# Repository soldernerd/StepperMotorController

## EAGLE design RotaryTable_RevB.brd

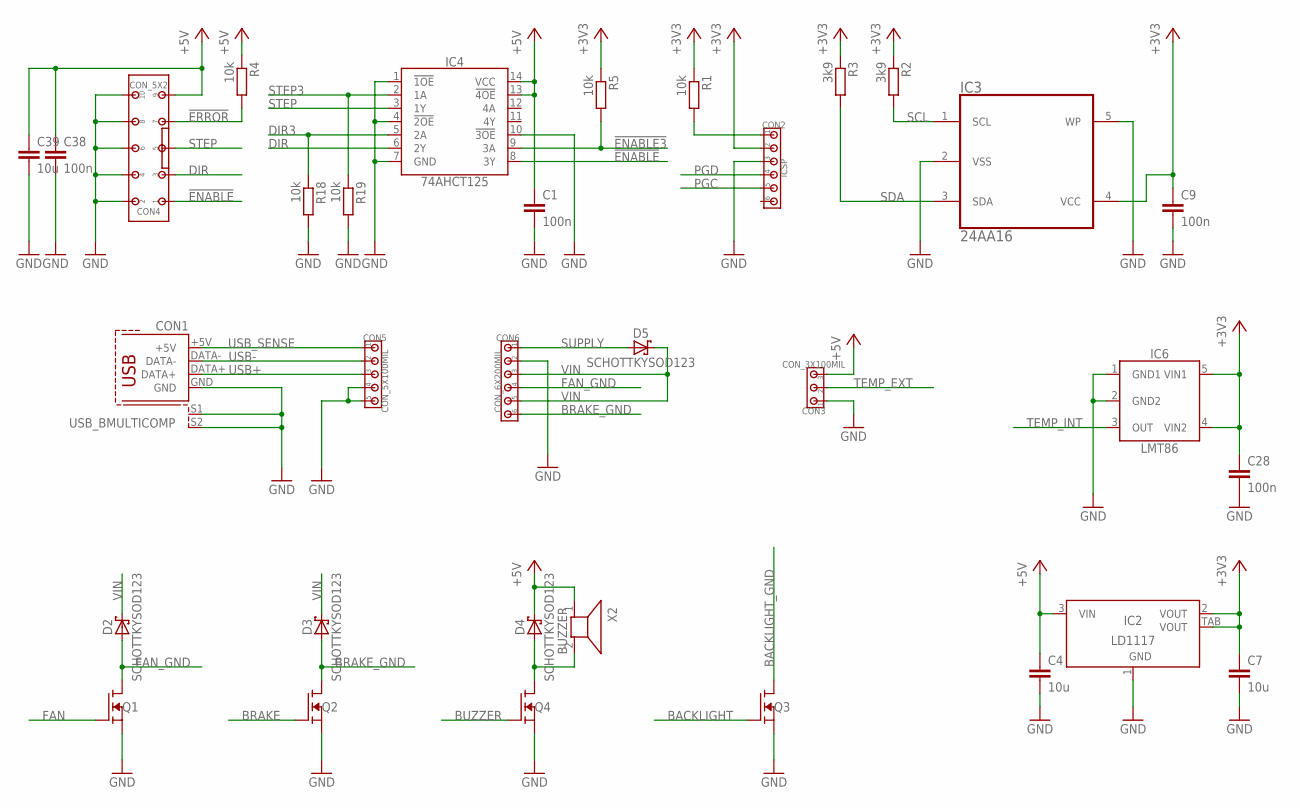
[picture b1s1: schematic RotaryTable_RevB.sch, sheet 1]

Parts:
C1, C9, C28, C38: 100n; C0805
C4, C7, C39: 10u; C0805
CON1: USB_BMULTICOMP; USB_B
CON2: ICSP; 100MIL_6X
CON3: CON_3X100MIL; 100MIL_3X
CON4: CON_5X2; 100MIL_5X2
CON5: CON_5X100MIL; 100MIL_5X
CON6: CON_6X200MIL; 200MIL_6X
D2, D3, D4, D5: SCHOTTKYSOD123; SOD123
IC2: LD1117; SOT223
IC3: 24AA16; SOT-23-5
IC4: 74AHCT125; SO14
IC6: LMT86; SC70-5
Q1, Q2, Q3, Q4: N-FETSOT23; SOT23
R1, R4, R5, R18, R19: 10k; R0805
R2, R3: 3k9; R0805
X2: BUZZER; BUZZER_14MM

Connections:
!ENABLE3!: IC4.9 (3A), R5.2; also elsewhere on the board
!ENABLE!: CON4.1, IC4.8 (3Y)
!ERROR!: CON4.7, R4.2; also elsewhere on the board
!MCLR!: CON2.1, R1.2; also elsewhere on the board
+3V3: C7.1, C9.1, C28.1, CON2.2, IC2.2 (VOUT), IC2.TAB (VOUT), IC3.4 (VCC), IC6.4 (VIN2), IC6.5 (VIN1), R1.1, R2.1, R3.1, R5.1; also elsewhere on the board
+5V: C1.1, C4.1, C38.1, C39.1, CON3.3, CON4.9, D4.C, IC2.3 (VIN), IC4.13 (!4OE!), IC4.14 (VCC), R4.1, X2.1; also elsewhere on the board
BACKLIGHT: Q3.1 (G); also elsewhere on the board
BACKLIGHT_GND: Q3.3 (D); also elsewhere on the board
BRAKE: Q2.1 (G); also elsewhere on the board
BRAKE_GND: CON6.6, D3.A, Q2.3 (D)
BUZZER: Q4.1 (G); also elsewhere on the board
BUZZER_GND: D4.A, Q4.3 (D), X2.2
DIR: CON4.3, IC4.6 (2Y)
DIR3: IC4.5 (2A), R18.1; also elsewhere on the board
FAN: Q1.1 (G); also elsewhere on the board
FAN_GND: CON6.4, D2.A, Q1.3 (D)
GND: C1.2, C4.2, C7.2, C9.2, C28.2, C38.2, C39.2, CON1.GND, CON1.S1, CON1.S2, CON2.3, CON3.1, CON4.2, CON4.4, CON4.6, CON4.8, CON4.10, CON5.4, CON5.5, CON6.2, IC2.1 (GND), IC3.2 (VSS), IC3.5 (WP), IC4.1 (!1OE!), IC4.4 (!2OE!), IC4.7 (GND), IC4.10 (!3OE!), IC6.1 (GND1), IC6.2 (GND2), Q1.2 (S), Q2.2 (S), Q3.2 (S), Q4.2 (S), R18.2, R19.2; also elsewhere on the board
PGC: CON2.5; also elsewhere on the board
PGD: CON2.4; also elsewhere on the board
SCL: IC3.1 (SCL), R2.2; also elsewhere on the board
SDA: IC3.3 (SDA), R3.2; also elsewhere on the board
STEP: CON4.5, IC4.3 (1Y)
STEP3: IC4.2 (1A), R19.1; also elsewhere on the board
SUPPLY: CON6.1, D5.A
TEMP_EXT: CON3.2; also elsewhere on the board
TEMP_INT: IC6.3 (OUT); also elsewhere on the board
USB+: CON1.DATA+, CON5.3; also elsewhere on the board
USB-: CON1.DATA-, CON5.2; also elsewhere on the board
USB_SENSE: CON1.+5V, CON5.1; also elsewhere on the board
VIN: CON6.3, CON6.5, D2.C, D3.C, D5.C; also elsewhere on the board

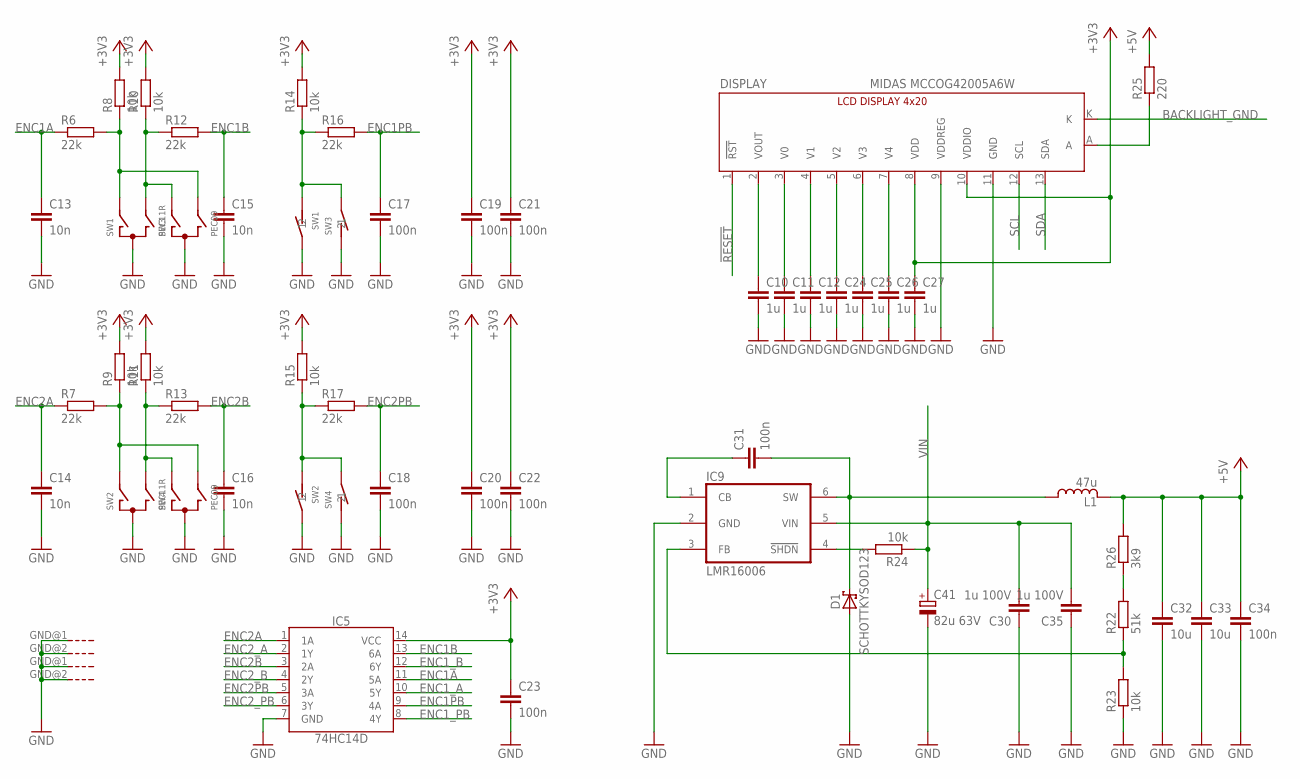
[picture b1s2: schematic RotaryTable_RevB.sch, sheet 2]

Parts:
C10, C11, C12, C24, C25, C26, C27: 1u; C0805
C13, C14, C15, C16: 10n; C0805
C17, C18, C19, C20, C21, C22, C23, C31, C34: 100n; C0805
C30, C35: 1u 100V; C0805
C32, C33: 10u; C0805
C41: 82u 63V; 8MM
D1: SCHOTTKYSOD123; SOD123
DISPLAY: MIDAS MCCOG42005A6W; LCD_4X20_I2C
IC5: 74HC14D; SO14
IC9: LMR16006; SOT-32-6
L1: 47u; SRN5040
R6, R7, R12, R13, R16, R17: 22k; R0805
R8, R9, R10, R11, R14, R15, R23, R24: 10k; R0805
R22: 51k; R0805
R25: 220; R0805
R26: 3k9; R0805
SW1, SW2: PEC11R; ENCODER_BOURNS
SW3, SW4: PEC09

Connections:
!RESET!: DISPLAY.1 (!RST!); also elsewhere on the board
+3V3: C19.1, C20.1, C21.1, C22.1, C23.1, C27.1, DISPLAY.8 (VDD), DISPLAY.10 (VDDIO), IC5.14 (VCC), R8.2, R9.2, R10.2, R11.2, R14.2, R15.2; also elsewhere on the board
+5V: C32.1, C33.1, C34.1, L1.2, R25.2, R26.2; also elsewhere on the board
BACKLIGHT_GND: DISPLAY.K; also elsewhere on the board
ENC1A: C13.1, IC5.11 (5A), R6.1
ENC1B: C15.1, IC5.13 (6A), R12.2
ENC1PB: C17.1, IC5.9 (4A), R16.2
ENC1_A: IC5.10 (5Y); also elsewhere on the board
ENC1_B: IC5.12 (6Y); also elsewhere on the board
ENC1_PB: IC5.8 (4Y); also elsewhere on the board
ENC2A: C14.1, IC5.1 (1A), R7.1
ENC2B: C16.1, IC5.3 (2A), R13.2
ENC2PB: C18.1, IC5.5 (3A), R17.2
ENC2_A: IC5.2 (1Y); also elsewhere on the board
ENC2_B: IC5.4 (2Y); also elsewhere on the board
ENC2_PB: IC5.6 (3Y); also elsewhere on the board
GND: C10.2, C11.2, C12.2, C13.2, C14.2, C15.2, C16.2, C17.2, C18.2, C19.2, C20.2, C21.2, C22.2, C23.2, C24.2, C25.2, C26.2, C27.2, C30.1, C32.2, C33.2, C34.2, C35.1, C41.-, D1.A, DISPLAY.9 (VDDREG), DISPLAY.11 (GND), IC5.7 (GND), IC9.2 (GND), R23.1, SW1.2, SW1.C, SW1.GND@1 (G), SW1.GND@2 (G), SW2.2, SW2.C, SW2.GND@1 (G), SW2.GND@2 (G), SW3.C, SW3.D (1), SW4.C, SW4.D (1); also elsewhere on the board
unnamed: IC9.4 (!SHDN!), R24.2
unnamed: C31.1, IC9.1 (CB)
unnamed: IC9.3 (FB), R22.1, R23.2
unnamed: R22.2, R26.1
unnamed: R15.1, R17.1, SW2.1, SW4.E (2)
unnamed: R10.1, R12.1, SW1.B, SW3.A
unnamed: R6.2, R8.1, SW1.A, SW3.B
unnamed: DISPLAY.A, R25.1
unnamed: R7.2, R9.1, SW2.A, SW4.B
unnamed: R14.1, R16.1, SW1.1, SW3.E (2)
unnamed: R11.1, R13.1, SW2.B, SW4.A
unnamed: C10.1, DISPLAY.2 (VOUT)
unnamed: C11.1, DISPLAY.3 (V0)
unnamed: C26.1, DISPLAY.7 (V4)
unnamed: C25.1, DISPLAY.6 (V3)
unnamed: C24.1, DISPLAY.5 (V2)
unnamed: C12.1, DISPLAY.4 (V1)
SCL: DISPLAY.12 (SCL); also elsewhere on the board
SDA: DISPLAY.13 (SDA); also elsewhere on the board
SWITCH: C31.2, D1.C, IC9.6 (SW), L1.1
VIN: C30.2, C35.2, C41.+, IC9.5 (VIN), R24.1; also elsewhere on the board

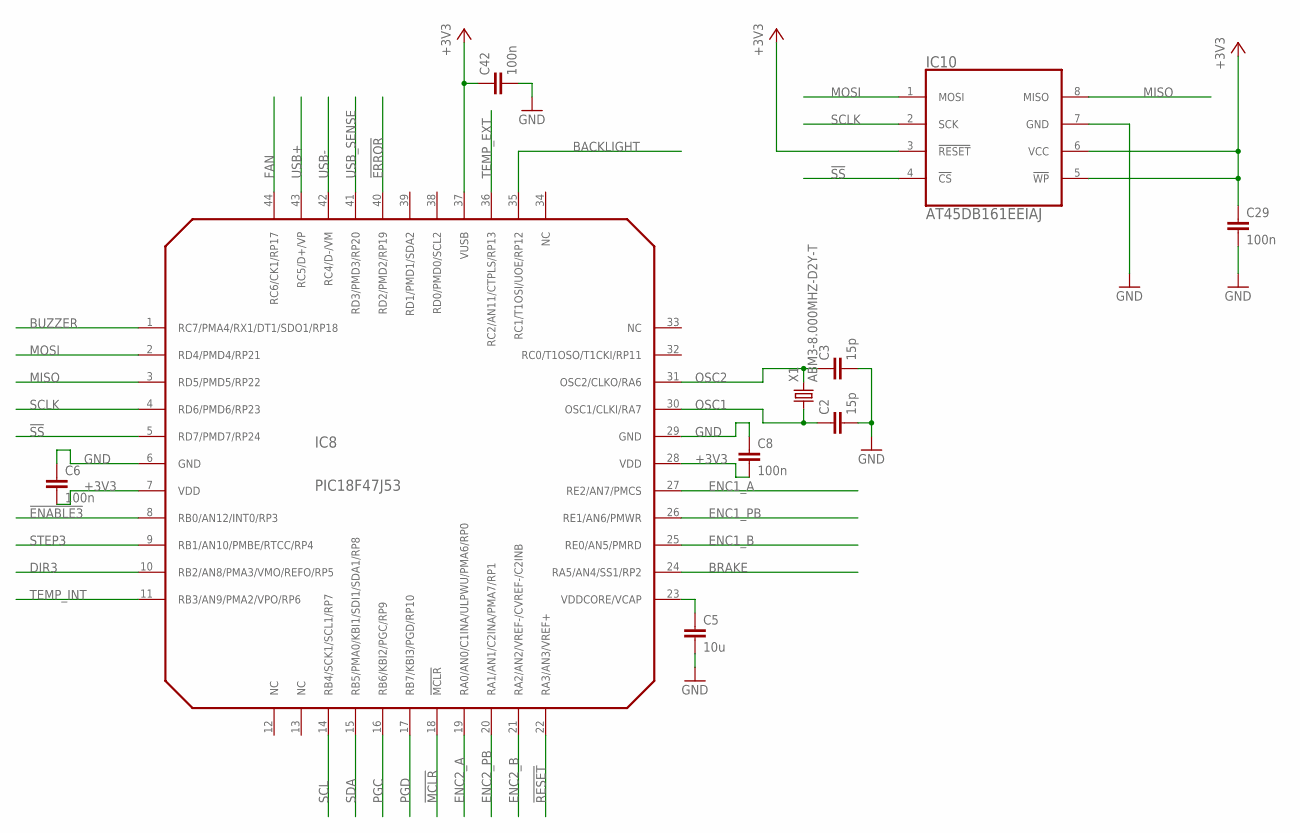
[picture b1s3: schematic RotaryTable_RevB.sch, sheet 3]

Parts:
C2, C3: 15p; C0805
C5: 10u; C0805
C6, C8, C29, C42: 100n; C0805
IC8: PIC18F47J53; TQFP44
IC10: AT45DB161EEIAJ; EIAJ_SOIC8
X1: ABM3-8.000MHZ-D2Y-T; 5X3.2MM

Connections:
!ENABLE3!: IC8.8 (RB0/AN12/INT0/RP3); also elsewhere on the board
!ERROR!: IC8.40 (RD2/PMD2/RP19); also elsewhere on the board
!MCLR!: IC8.18 (!MCLR!); also elsewhere on the board
!RESET!: IC8.22 (RA3/AN3/VREF+); also elsewhere on the board
!SS!: IC8.5 (RD7/PMD7/RP24), IC10.4 (!CS!)
+3V3: C6.2, C8.2, C29.1, C42.1, IC8.7 (VDD), IC8.28 (VDD), IC8.37 (VUSB), IC10.3 (!RESET!), IC10.5 (!WP!), IC10.6 (VCC); also elsewhere on the board
BACKLIGHT: IC8.35 (RC1/T1OSI/UOE/RP12); also elsewhere on the board
BRAKE: IC8.24 (RA5/AN4/SS1/RP2); also elsewhere on the board
BUZZER: IC8.1 (RC7/PMA4/RX1/DT1/SDO1/RP18); also elsewhere on the board
DIR3: IC8.10 (RB2/AN8/PMA3/VMO/REFO/RP5); also elsewhere on the board
ENC1_A: IC8.27 (RE2/AN7/PMCS); also elsewhere on the board
ENC1_B: IC8.25 (RE0/AN5/PMRD); also elsewhere on the board
ENC1_PB: IC8.26 (RE1/AN6/PMWR); also elsewhere on the board
ENC2_A: IC8.19 (RA0/AN0/C1INA/ULPWU/PMA6/RP0); also elsewhere on the board
ENC2_B: IC8.21 (RA2/AN2/VREF-/CVREF-/C2INB); also elsewhere on the board
ENC2_PB: IC8.20 (RA1/AN1/C2INA/PMA7/RP1); also elsewhere on the board
FAN: IC8.44 (RC6/CK1/RP17); also elsewhere on the board
GND: C2.2, C3.2, C5.2, C6.1, C8.1, C29.2, C42.2, IC8.6 (GND), IC8.29 (GND), IC10.7 (GND); also elsewhere on the board
MISO: IC8.3 (RD5/PMD5/RP22), IC10.8 (MISO)
MOSI: IC8.2 (RD4/PMD4/RP21), IC10.1 (MOSI)
unnamed: C5.1, IC8.23 (VDDCORE/VCAP)
OSC1: C2.1, IC8.30 (OSC1/CLKI/RA7), X1.1
OSC2: C3.1, IC8.31 (OSC2/CLKO/RA6), X1.2
PGC: IC8.16 (RB6/KBI2/PGC/RP9); also elsewhere on the board
PGD: IC8.17 (RB7/KBI3/PGD/RP10); also elsewhere on the board
SCL: IC8.14 (RB4/SCK1/SCL1/RP7); also elsewhere on the board
SCLK: IC8.4 (RD6/PMD6/RP23), IC10.2 (SCK)
SDA: IC8.15 (RB5/PMA0/KBI1/SDI1/SDA1/RP8); also elsewhere on the board
STEP3: IC8.9 (RB1/AN10/PMBE/RTCC/RP4); also elsewhere on the board
TEMP_EXT: IC8.36 (RC2/AN11/CTPLS/RP13); also elsewhere on the board
TEMP_INT: IC8.11 (RB3/AN9/PMA2/VPO/RP6); also elsewhere on the board
USB+: IC8.43 (RC5/D+/VP); also elsewhere on the board
USB-: IC8.42 (RC4/D-/VM); also elsewhere on the board
USB_SENSE: IC8.41 (RD3/PMD3/RP20); also elsewhere on the board

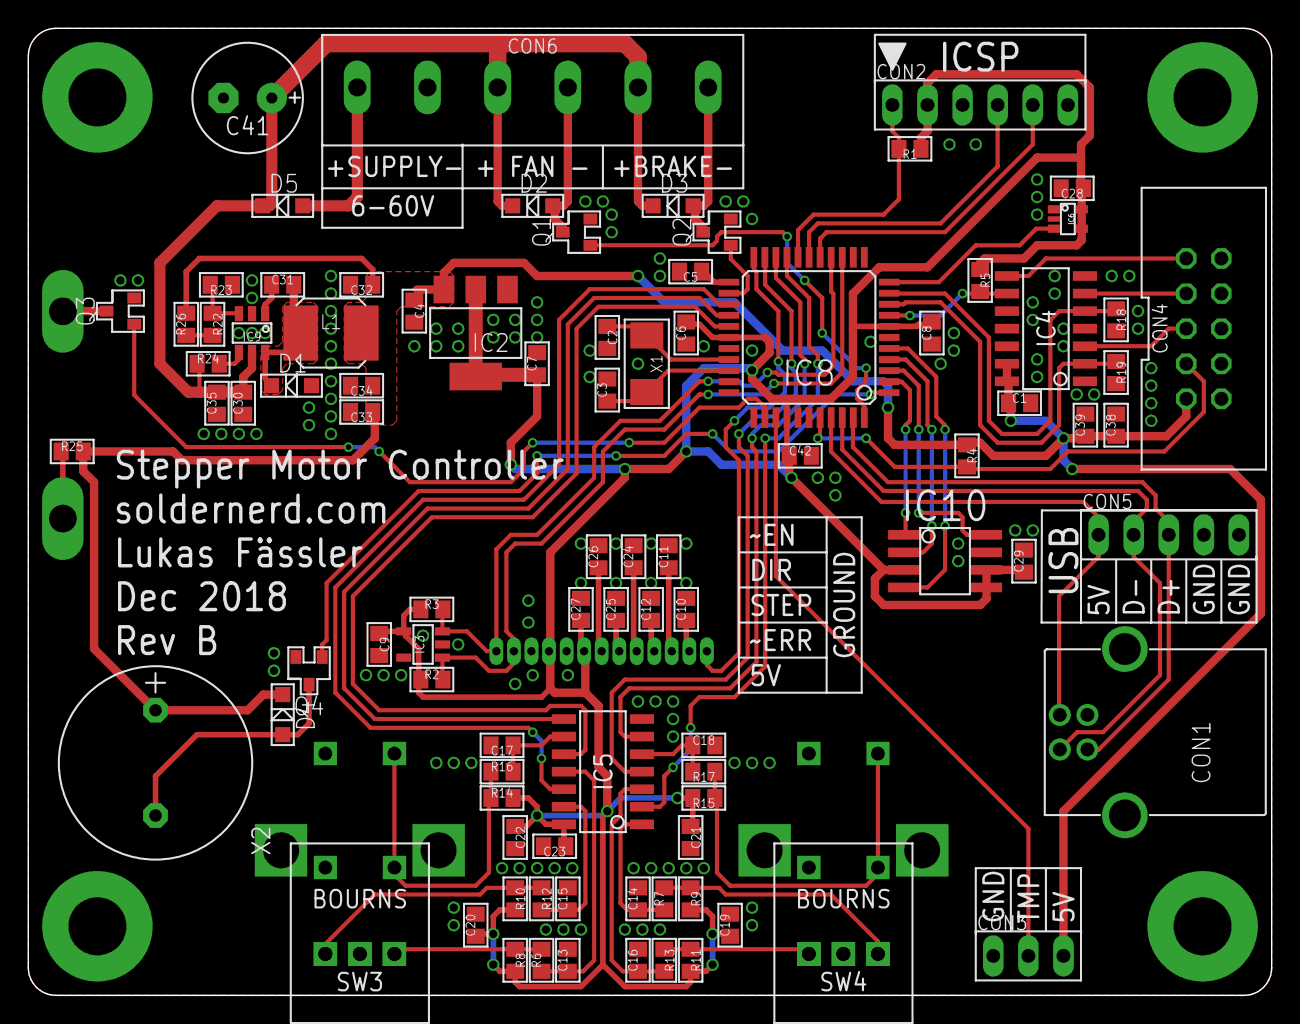
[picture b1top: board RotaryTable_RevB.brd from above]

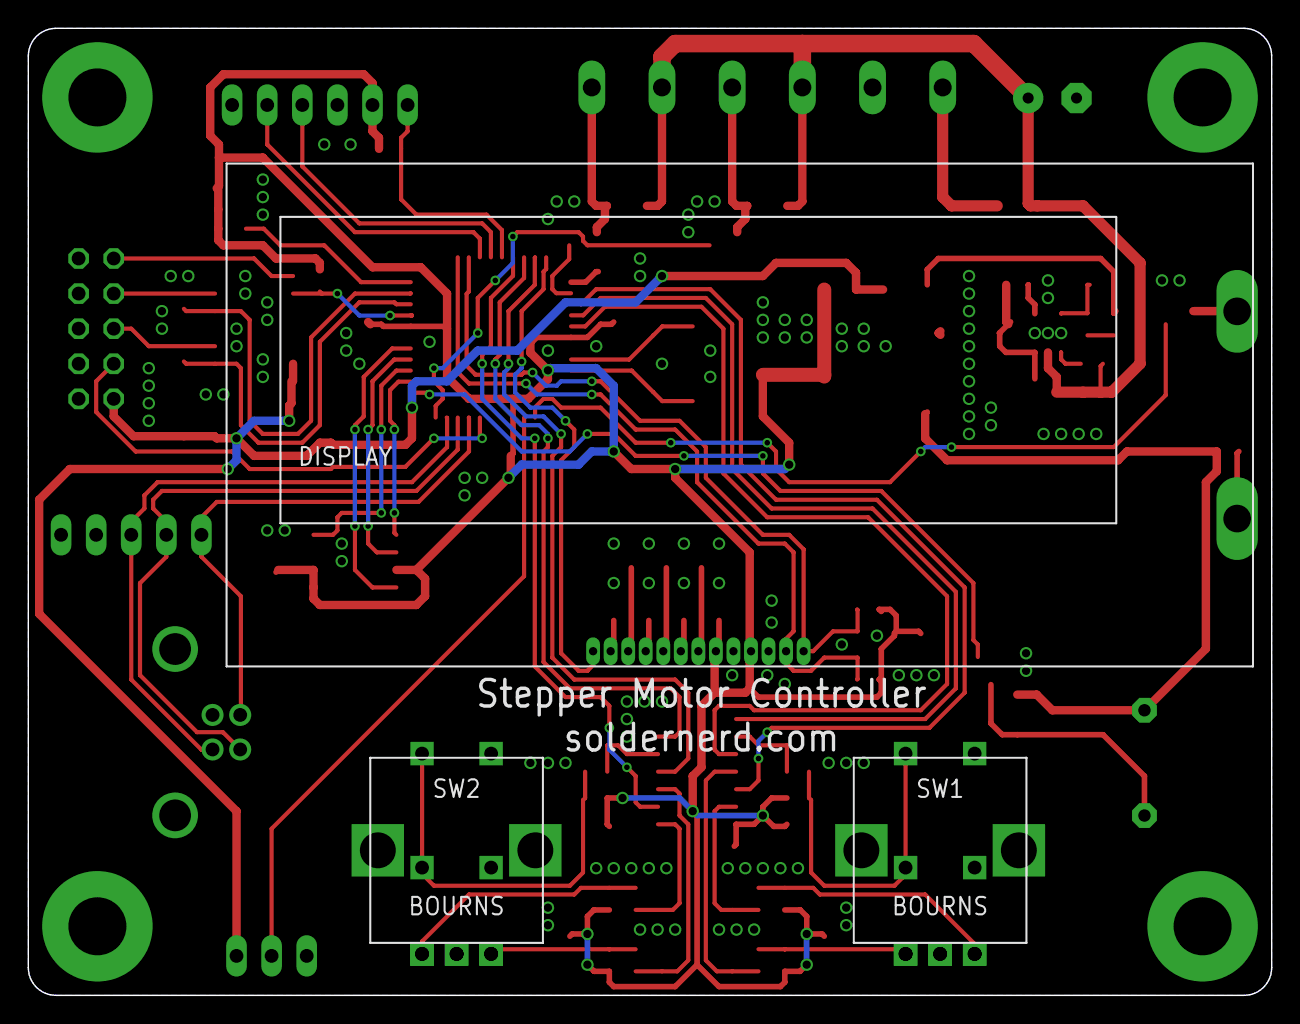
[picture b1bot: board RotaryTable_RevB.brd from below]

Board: 2 copper layers, 90.0 x 70.0 mm, 94 parts (3 on the bottom side), 68 nets.

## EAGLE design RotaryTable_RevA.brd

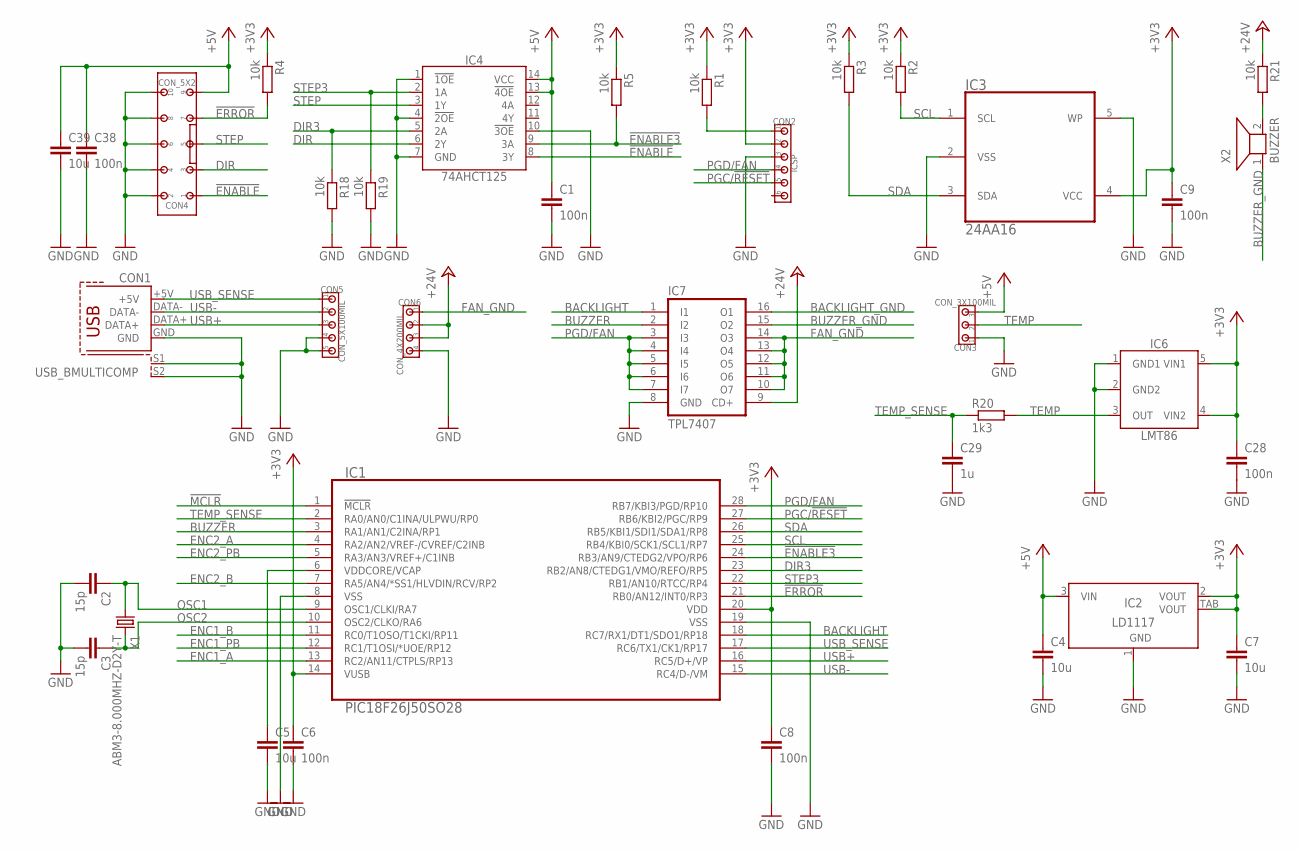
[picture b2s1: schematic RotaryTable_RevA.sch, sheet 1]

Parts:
C1, C6, C8, C9, C28, C38: 100n; C0805
C2, C3: 15p; C0805
C4, C5, C7, C39: 10u; C0805
C29: 1u; C0805
CON1: USB_BMULTICOMP; USB_B
CON2: ICSP; 100MIL_6X
CON3: CON_3X100MIL; 100MIL_3X
CON4: CON_5X2; 100MIL_5X2
CON5: CON_5X100MIL; 100MIL_5X
CON6: CON_4X200MIL; 200MIL_4X
IC1: PIC18F26J50SO28; SO28W
IC2: LD1117; SOT223
IC3: 24AA16; SOT-23-5
IC4: 74AHCT125; SO14
IC6: LMT86; SC70-5
IC7: TPL7407; SO16
R1, R2, R3, R4, R5, R18, R19, R21: 10k; R0805
R20: 1k3; R0805
X1: ABM3-8.000MHZ-D2Y-T; 5X3.2MM
X2: BUZZER; BUZZER_14MM

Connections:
!ENABLE3!: IC1.24 (RB3/AN9/CTEDG2/VPO/RP6), IC4.9 (3A), R5.2
!ENABLE!: CON4.1, IC4.8 (3Y)
!ERROR!: CON4.7, IC1.21 (RB0/AN12/INT0/RP3), R4.2
!MCLR!: CON2.1, IC1.1 (!MCLR!), R1.2
+3V3: C6.1, C7.1, C8.1, C9.1, C28.1, CON2.2, IC1.14 (VUSB), IC1.20 (VDD), IC2.2 (VOUT), IC2.TAB (VOUT), IC3.4 (VCC), IC6.4 (VIN2), IC6.5 (VIN1), R1.1, R2.1, R3.1, R4.1, R5.1; also elsewhere on the board
+5V: C1.1, C4.1, C38.1, C39.1, CON3.3, CON4.9, IC2.3 (VIN), IC4.13 (!4OE!), IC4.14 (VCC); also elsewhere on the board
+24V: CON6.2, CON6.3, IC7.9 (CD+), R21.1; also elsewhere on the board
BACKLIGHT: IC1.18 (RC7/RX1/DT1/SDO1/RP18), IC7.1 (I1)
BACKLIGHT_GND: IC7.16 (O1); also elsewhere on the board
BUZZER: IC1.3 (RA1/AN1/C2INA/RP1), IC7.2 (I2)
BUZZER_GND: IC7.15 (O2), X2.1
DIR: CON4.3, IC4.6 (2Y)
DIR3: IC1.23 (RB2/AN8/CTEDG1/VMO/REFO/RP5), IC4.5 (2A), R18.1
ENC1_A: IC1.13 (RC2/AN11/CTPLS/RP13); also elsewhere on the board
ENC1_B: IC1.11 (RC0/T1OSO/T1CKI/RP11); also elsewhere on the board
ENC1_PB: IC1.12 (RC1/T1OSI/*UOE/RP12); also elsewhere on the board
ENC2_A: IC1.4 (RA2/AN2/VREF-/CVREF/C2INB); also elsewhere on the board
ENC2_B: IC1.7 (RA5/AN4/*SS1/HLVDIN/RCV/RP2); also elsewhere on the board
ENC2_PB: IC1.5 (RA3/AN3/VREF+/C1INB); also elsewhere on the board
FAN_GND: CON6.1, IC7.10 (O7), IC7.11 (O6), IC7.12 (O5), IC7.13 (O4), IC7.14 (O3)
GND: C1.2, C2.2, C3.2, C4.2, C5.2, C6.2, C7.2, C8.2, C9.2, C28.2, C29.2, C38.2, C39.2, CON1.GND, CON1.S1, CON1.S2, CON2.3, CON3.1, CON4.2, CON4.4, CON4.6, CON4.8, CON4.10, CON5.4, CON5.5, CON6.4, IC1.8 (VSS), IC1.19 (VSS), IC2.1 (GND), IC3.2 (VSS), IC3.5 (WP), IC4.1 (!1OE!), IC4.4 (!2OE!), IC4.7 (GND), IC4.10 (!3OE!), IC6.1 (GND1), IC6.2 (GND2), IC7.8 (GND), R18.2, R19.2; also elsewhere on the board
unnamed: C5.1, IC1.6 (VDDCORE/VCAP)
unnamed: R21.2, X2.2
OSC1: C2.1, IC1.9 (OSC1/CLKI/RA7), X1.1
OSC2: C3.1, IC1.10 (OSC2/CLKO/RA6), X1.2
PGC/!RESET!: CON2.5, IC1.27 (RB6/KBI2/PGC/RP9); also elsewhere on the board
PGD/FAN: CON2.4, IC1.28 (RB7/KBI3/PGD/RP10), IC7.3 (I3), IC7.4 (I4), IC7.5 (I5), IC7.6 (I6), IC7.7 (I7)
SCL: IC1.25 (RB4/KBI0/SCK1/SCL1/RP7), IC3.1 (SCL), R2.2; also elsewhere on the board
SDA: IC1.26 (RB5/KBI1/SDI1/SDA1/RP8), IC3.3 (SDA), R3.2; also elsewhere on the board
STEP: CON4.5, IC4.3 (1Y)
STEP3: IC1.22 (RB1/AN10/RTCC/RP4), IC4.2 (1A), R19.1
TEMP: CON3.2, IC6.3 (OUT), R20.2
TEMP_SENSE: C29.1, IC1.2 (RA0/AN0/C1INA/ULPWU/RP0), R20.1
USB+: CON1.DATA+, CON5.3, IC1.16 (RC5/D+/VP)
USB-: CON1.DATA-, CON5.2, IC1.15 (RC4/D-/VM)
USB_SENSE: CON1.+5V, CON5.1, IC1.17 (RC6/TX1/CK1/RP17)

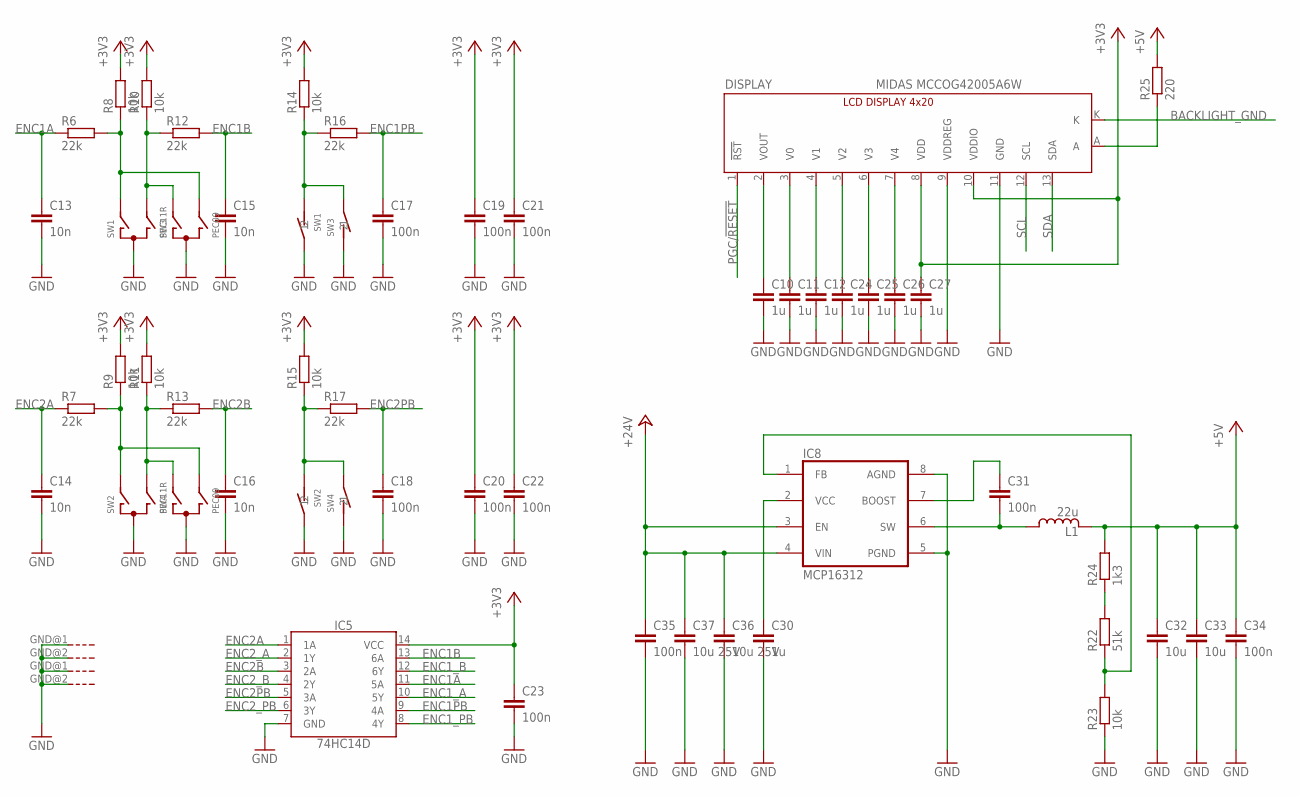
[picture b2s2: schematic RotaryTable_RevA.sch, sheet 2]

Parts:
C10, C11, C12, C24, C25, C26, C27, C30: 1u; C0805
C13, C14, C15, C16: 10n; C0805
C17, C18, C19, C20, C21, C22, C23, C31, C34, C35: 100n; C0805
C32, C33: 10u; C0805
C36, C37: 10u 25V; C1206
DISPLAY: MIDAS MCCOG42005A6W; LCD_4X20_I2C
IC5: 74HC14D; SO14
IC8: MCP16312; MSOP8
L1: 22u; SRN5040
R6, R7, R12, R13, R16, R17: 22k; R0805
R8, R9, R10, R11, R14, R15, R23: 10k; R0805
R22: 51k; R0805
R24: 1k3; R0805
R25: 220; R0805
SW1, SW2: PEC11R; ENCODER_BOURNS
SW3, SW4: PEC09

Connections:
+3V3: C19.1, C20.1, C21.1, C22.1, C23.1, C27.1, DISPLAY.8 (VDD), DISPLAY.10 (VDDIO), IC5.14 (VCC), R8.2, R9.2, R10.2, R11.2, R14.2, R15.2; also elsewhere on the board
+5V: C32.1, C33.1, C34.1, L1.2, R24.2, R25.2; also elsewhere on the board
+24V: C35.1, C36.1, C37.1, IC8.3 (EN), IC8.4 (VIN); also elsewhere on the board
BACKLIGHT_GND: DISPLAY.K; also elsewhere on the board
ENC1A: C13.1, IC5.11 (5A), R6.1
ENC1B: C15.1, IC5.13 (6A), R12.2
ENC1PB: C17.1, IC5.9 (4A), R16.2
ENC1_A: IC5.10 (5Y); also elsewhere on the board
ENC1_B: IC5.12 (6Y); also elsewhere on the board
ENC1_PB: IC5.8 (4Y); also elsewhere on the board
ENC2A: C14.1, IC5.1 (1A), R7.1
ENC2B: C16.1, IC5.3 (2A), R13.2
ENC2PB: C18.1, IC5.5 (3A), R17.2
ENC2_A: IC5.2 (1Y); also elsewhere on the board
ENC2_B: IC5.4 (2Y); also elsewhere on the board
ENC2_PB: IC5.6 (3Y); also elsewhere on the board
GND: C10.2, C11.2, C12.2, C13.2, C14.2, C15.2, C16.2, C17.2, C18.2, C19.2, C20.2, C21.2, C22.2, C23.2, C24.2, C25.2, C26.2, C27.2, C30.2, C32.2, C33.2, C34.2, C35.2, C36.2, C37.2, DISPLAY.9 (VDDREG), DISPLAY.11 (GND), IC5.7 (GND), IC8.5 (PGND), IC8.8 (AGND), R23.1, SW1.2, SW1.C, SW1.GND@1 (G), SW1.GND@2 (G), SW2.2, SW2.C, SW2.GND@1 (G), SW2.GND@2 (G), SW3.C, SW3.D (1), SW4.C, SW4.D (1); also elsewhere on the board
unnamed: C31.2, IC8.6 (SW), L1.1
unnamed: C30.1, IC8.2 (VCC)
unnamed: IC8.1 (FB), R22.1, R23.2
unnamed: C31.1, IC8.7 (BOOST)
unnamed: R22.2, R24.1
unnamed: R15.1, R17.1, SW2.1, SW4.E (2)
unnamed: R10.1, R12.1, SW1.B, SW3.A
unnamed: R6.2, R8.1, SW1.A, SW3.B
unnamed: DISPLAY.A, R25.1
unnamed: R7.2, R9.1, SW2.A, SW4.B
unnamed: R14.1, R16.1, SW1.1, SW3.E (2)
unnamed: R11.1, R13.1, SW2.B, SW4.A
unnamed: C10.1, DISPLAY.2 (VOUT)
unnamed: C11.1, DISPLAY.3 (V0)
unnamed: C26.1, DISPLAY.7 (V4)
unnamed: C25.1, DISPLAY.6 (V3)
unnamed: C24.1, DISPLAY.5 (V2)
unnamed: C12.1, DISPLAY.4 (V1)
PGC/!RESET!: DISPLAY.1 (!RST!); also elsewhere on the board
SCL: DISPLAY.12 (SCL); also elsewhere on the board
SDA: DISPLAY.13 (SDA); also elsewhere on the board

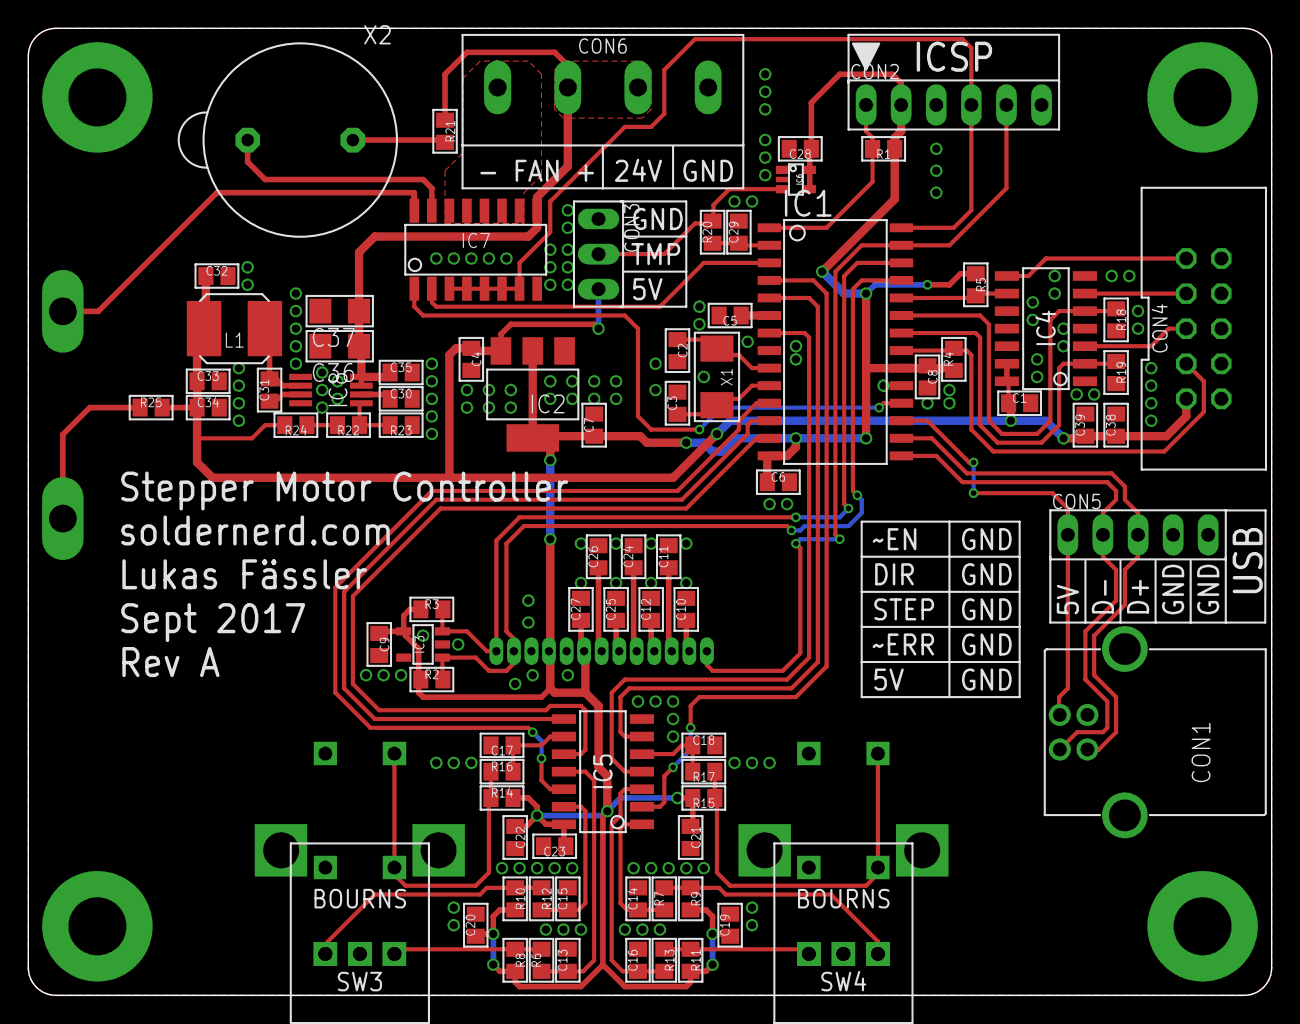
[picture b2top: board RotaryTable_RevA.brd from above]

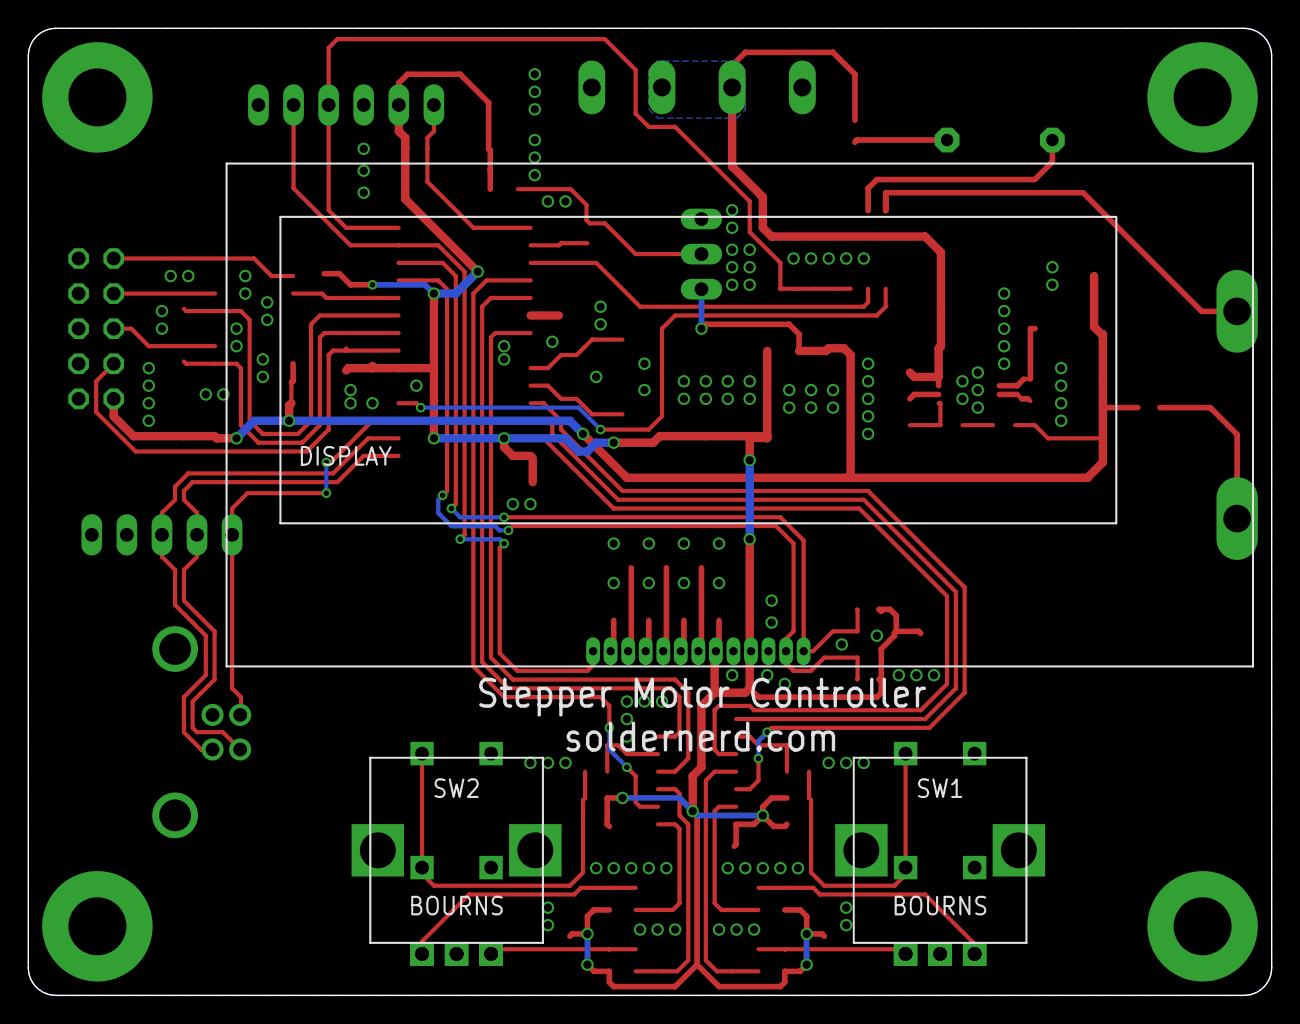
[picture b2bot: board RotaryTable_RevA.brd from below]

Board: 2 copper layers, 90.0 x 70.0 mm, 86 parts (3 on the bottom side), 60 nets.

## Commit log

2017-09-09 Revision A completed
2017-09-10 USB header changed, header for external temperature sensor added, some ground vias added
2017-10-01 Bug related to external temperature sensing fixed
2018-06-23 Error in schematic and in board layout fixed. Voltage regulator feedback was taken from the wrong side of the coil.
2019-01-06 Revision B final
